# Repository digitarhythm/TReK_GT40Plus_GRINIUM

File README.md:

# TReK_GT40Plus_GRINIUM
KiCAD project for TReK GT40Plus GRINIUM

Firmware: https://github.com/digitarhythm/qmk_firmware/tree/grinium/keyboards/trek/grinium

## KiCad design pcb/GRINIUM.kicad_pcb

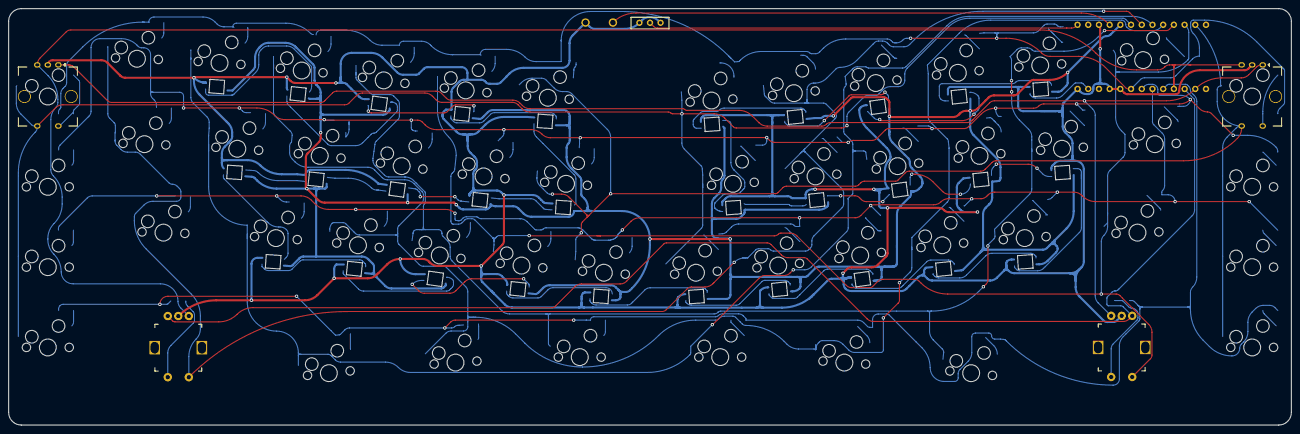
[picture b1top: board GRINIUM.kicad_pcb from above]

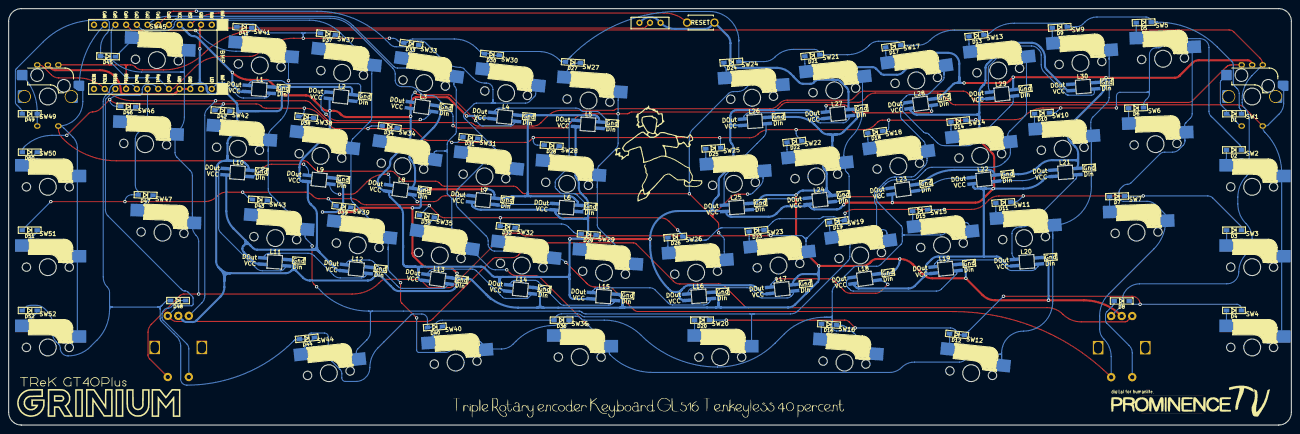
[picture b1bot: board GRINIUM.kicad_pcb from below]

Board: 2 copper layers, 304.4 x 98.8 mm, 141 parts (4 on the bottom side), 100 nets.

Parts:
D1, D2, D3, D4, D5, D6, D7, D8, D9, D10, D11, D12, D13, D14, D15, D16, D17, D18, D19, D20, D21, D22, D23, D24, D25, D26, D27, D28, D29, D30, D31, D32, D33, D34, D35, D36, D37, D38, D39, D40, D41, D42, D43, D44, D45, D46, D47, D48, D49, D50, D51, D52: D; Diode_SMD
G001, G002, G003, G004: LOGO
J1: Conn_01x02; Battery_XH2.5_GL_PCB
L1, L2, L3, L4, L5, L6, L7, L8, L9, L10, L11, L12, L13, L14, L15, L16, L17, L18, L19, L20, L21, L22, L23, L24, L25, L26, L27, L28, L29, L30: SK6812MINI; LED_SK6812MINI-E_BL
SW1, SW49: RotaryEncoder_Switch; SW_Cherry_MX_1.00u_Kailh_EC12
SW2, SW3, SW4, SW5, SW9, SW10, SW11, SW13, SW14, SW15, SW17, SW18, SW19, SW21, SW22, SW23, SW24, SW25, SW26, SW27, SW28, SW29, SW30, SW31, SW32, SW33, SW34, SW35, SW37, SW38, SW39, SW41, SW42, SW43, SW50, SW51, SW52: SW_PUSH; CherryMX_Hotswap_1u
SW6, SW12, SW20, SW36, SW44, SW46: SW_PUSH; CherryMX_Hotswap_1.25u
SW7, SW16, SW40, SW47: SW_PUSH; CherryMX_Hotswap_1.75u
SW8, SW48: RotaryEncoder_Switch; RotaryEncoder_EC12E
SW45: SW_PUSH; CherryMX_Hotswap_1.5u
SW53: SW_PUSH; ResetSW
U1: BLEMicroPro; Micon_BMP_GL

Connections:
Bat+: J1.1, U1.25 (BAT+)
Col0: SW1.S2, SW2.1, SW3.1, SW4.1, SW27.1, SW28.1, SW29.1, U1.20 (F4/PIN20)
Col1: SW5.1, SW6.1, SW7.1, SW8.S2, SW30.1, SW31.1, SW32.1, U1.19 (F5/PIN19)
Col2: SW9.1, SW10.1, SW11.1, SW12.1, SW33.1, SW34.1, SW35.1, SW36.1, U1.18 (F6/PIN18)
Col3: SW13.1, SW14.1, SW15.1, SW16.1, SW37.1, SW38.1, SW39.1, SW40.1, U1.17 (F7/PIN17)
Col4: SW17.1, SW18.1, SW19.1, SW20.1, SW41.1, SW42.1, SW43.1, SW44.1, U1.16 (B1/PIN16)
Col5: SW21.1, SW22.1, SW23.1, SW45.1, SW46.1, SW47.1, SW48.S2, U1.15 (B3/PIN15)
Col6: SW24.1, SW25.1, SW26.1, SW49.S2, SW50.1, SW51.1, SW52.1, U1.14 (B2/PIN14)
GND: J1.2, L1.2 (VSS), L2.2 (VSS), L3.2 (VSS), L4.2 (VSS), L5.2 (VSS), L6.2 (VSS), L7.2 (VSS), L8.2 (VSS), L9.2 (VSS), L10.2 (VSS), L11.2 (VSS), L12.2 (VSS), L13.2 (VSS), L14.2 (VSS), L15.2 (VSS), L16.2 (VSS), L17.2 (VSS), L18.2 (VSS), L19.2 (VSS), L20.2 (VSS), L21.2 (VSS), L22.2 (VSS), L23.2 (VSS), L24.2 (VSS), L25.2 (VSS), L26.2 (VSS), L27.2 (VSS), L28.2 (VSS), L29.2 (VSS), L30.2 (VSS), SW1.C, SW8.C, SW48.C, SW49.C, SW53.2, U1.3 (GND), U1.4 (GND), U1.23 (GND), U1.26 (BAT-)
LED: L1.3 (DIN), U1.1 (D3/PIN1)
unnamed: D1.2 (A), SW1.S1
unnamed: D2.2 (A), SW2.2
unnamed: D3.2 (A), SW3.2
unnamed: D4.2 (A), SW4.2
unnamed: D5.2 (A), SW5.2
unnamed: D6.2 (A), SW6.2
unnamed: D7.2 (A), SW7.2
unnamed: D8.2 (A), SW8.S1
unnamed: D9.2 (A), SW9.2
unnamed: D10.2 (A), SW10.2
unnamed: D11.2 (A), SW11.2
unnamed: D12.2 (A), SW12.2
unnamed: D13.2 (A), SW13.2
unnamed: D14.2 (A), SW14.2
unnamed: D15.2 (A), SW15.2
unnamed: D16.2 (A), SW16.2
unnamed: D17.2 (A), SW17.2
unnamed: D18.2 (A), SW18.2
unnamed: D19.2 (A), SW19.2
unnamed: D20.2 (A), SW20.2
unnamed: D21.2 (A), SW21.2
unnamed: D22.2 (A), SW22.2
unnamed: D23.2 (A), SW23.2
unnamed: D24.2 (A), SW24.2
unnamed: D25.2 (A), SW25.2
unnamed: D26.2 (A), SW26.2
unnamed: D27.1 (K), SW27.2
unnamed: D28.1 (K), SW28.2
unnamed: D29.1 (K), SW29.2
unnamed: D30.1 (K), SW30.2
unnamed: D31.1 (K), SW31.2
unnamed: D32.1 (K), SW32.2
unnamed: D33.1 (K), SW33.2
unnamed: D34.1 (K), SW34.2
unnamed: D35.1 (K), SW35.2
unnamed: D36.1 (K), SW36.2
unnamed: D37.1 (K), SW37.2
unnamed: D38.1 (K), SW38.2
unnamed: D39.1 (K), SW39.2
unnamed: D40.1 (K), SW40.2
unnamed: D41.1 (K), SW41.2
unnamed: D42.1 (K), SW42.2
unnamed: D43.1 (K), SW43.2
unnamed: D44.1 (K), SW44.2
unnamed: D45.1 (K), SW45.2
unnamed: D46.1 (K), SW46.2
unnamed: D47.1 (K), SW47.2
unnamed: D48.1 (K), SW48.S1
unnamed: D49.1 (K), SW49.S1
unnamed: D50.1 (K), SW50.2
unnamed: D51.1 (K), SW51.2
unnamed: D52.1 (K), SW52.2
unnamed: L1.1 (DOUT), L2.3 (DIN)
unnamed: L2.1 (DOUT), L3.3 (DIN)
unnamed: L3.1 (DOUT), L4.3 (DIN)
unnamed: L4.1 (DOUT), L5.3 (DIN)
unnamed: L5.1 (DOUT), L6.3 (DIN)
unnamed: L6.1 (DOUT), L7.3 (DIN)
unnamed: L7.1 (DOUT), L8.3 (DIN)
unnamed: L8.1 (DOUT), L9.3 (DIN)
unnamed: L10.1 (DOUT), L11.3 (DIN)
unnamed: L9.1 (DOUT), L10.3 (DIN)
unnamed: L11.1 (DOUT), L12.3 (DIN)
unnamed: L12.1 (DOUT), L13.3 (DIN)
unnamed: L13.1 (DOUT), L14.3 (DIN)
unnamed: L14.1 (DOUT), L15.3 (DIN)
unnamed: L15.1 (DOUT), L16.3 (DIN)
unnamed: L16.1 (DOUT), L17.3 (DIN)
unnamed: L17.1 (DOUT), L18.3 (DIN)
unnamed: L18.1 (DOUT), L19.3 (DIN)
unnamed: L19.1 (DOUT), L20.3 (DIN)
unnamed: L20.1 (DOUT), L21.3 (DIN)
unnamed: L21.1 (DOUT), L22.3 (DIN)
unnamed: L22.1 (DOUT), L23.3 (DIN)
unnamed: L23.1 (DOUT), L24.3 (DIN)
unnamed: L24.1 (DOUT), L25.3 (DIN)
unnamed: L25.1 (DOUT), L26.3 (DIN)
unnamed: L26.1 (DOUT), L27.3 (DIN)
unnamed: L27.1 (DOUT), L28.3 (DIN)
unnamed: L28.1 (DOUT), L29.3 (DIN)
unnamed: L29.1 (DOUT), L30.3 (DIN)
RE01: SW1.B, SW8.A, SW49.B, U1.9 (D7/PIN9)
RE02: SW8.B, SW48.A, U1.10 (E6/PIN10)
RE03: SW1.A, SW48.B, SW49.A, U1.11 (B4/PIN11)
Reset: SW53.1, U1.22 (RST)
Row0: D1.1 (K), D5.1 (K), D9.1 (K), D13.1 (K), D17.1 (K), D21.1 (K), D24.1 (K), D27.2 (A), D30.2 (A), D33.2 (A), D37.2 (A), D41.2 (A), D45.2 (A), D49.2 (A), U1.5 (D1/PIN5/SDA)
Row1: D2.1 (K), D6.1 (K), D10.1 (K), D14.1 (K), D18.1 (K), D22.1 (K), D25.1 (K), D28.2 (A), D31.2 (A), D34.2 (A), D38.2 (A), D42.2 (A), D46.2 (A), D50.2 (A), U1.6 (D0/PIN6/SCL)
Row2: D3.1 (K), D7.1 (K), D11.1 (K), D15.1 (K), D19.1 (K), D23.1 (K), D26.1 (K), D29.2 (A), D32.2 (A), D35.2 (A), D39.2 (A), D43.2 (A), D47.2 (A), D51.2 (A), U1.7 (D4/PIN7)
Row3: D4.1 (K), D8.1 (K), D12.1 (K), D16.1 (K), D20.1 (K), D36.2 (A), D40.2 (A), D44.2 (A), D48.2 (A), D52.2 (A), U1.8 (C6/PIN8)
VCC: L1.4 (VDD), L2.4 (VDD), L3.4 (VDD), L4.4 (VDD), L5.4 (VDD), L6.4 (VDD), L7.4 (VDD), L8.4 (VDD), L9.4 (VDD), L10.4 (VDD), L11.4 (VDD), L12.4 (VDD), L13.4 (VDD), L14.4 (VDD), L15.4 (VDD), L16.4 (VDD), L17.4 (VDD), L18.4 (VDD), L19.4 (VDD), L20.4 (VDD), L21.4 (VDD), L22.4 (VDD), L23.4 (VDD), L24.4 (VDD), L25.4 (VDD), L26.4 (VDD), L27.4 (VDD), L28.4 (VDD), L29.4 (VDD), L30.4 (VDD), U1.21 (VCC)

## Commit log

2024-01-30 update licence file
2024-04-06 update LICENCE
